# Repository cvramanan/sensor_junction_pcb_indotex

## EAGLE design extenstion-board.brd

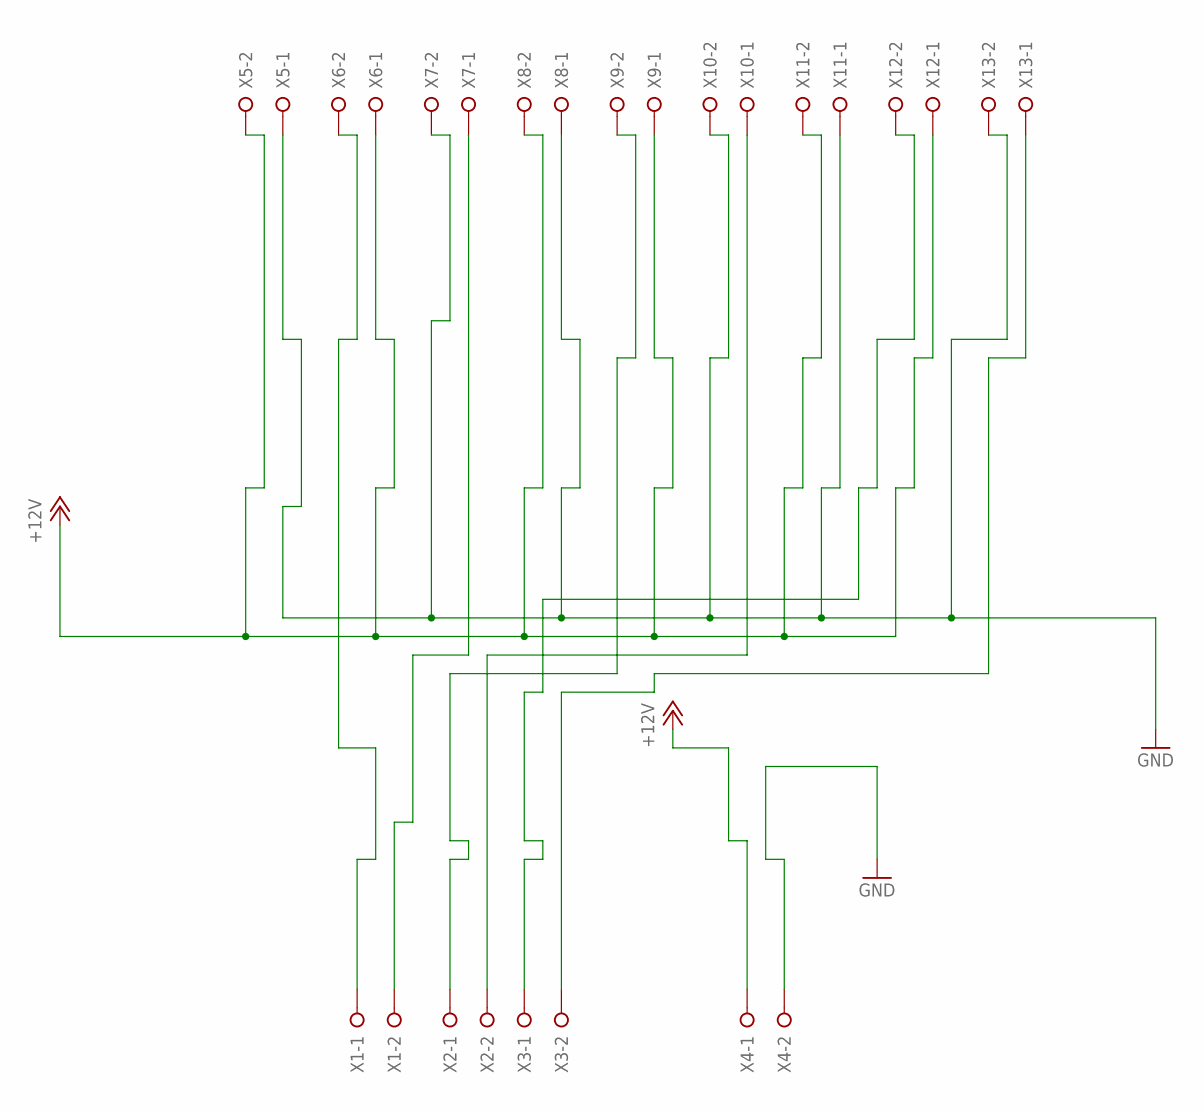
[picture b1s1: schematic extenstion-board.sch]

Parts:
X1, X2, X3, X4, X5, X6, X7, X8, X9, X10, X11, X12, X13: W237-02P; W237-132

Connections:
+12V: X4.1, X5.2, X6.1, X8.2, X9.1, X11.2, X12.1
GND: X4.2, X5.1, X7.2, X8.1, X10.2, X11.1, X13.2
unnamed: X3.1, X12.2
unnamed: X1.1, X6.2
unnamed: X1.2, X7.1
unnamed: X2.1, X9.2
unnamed: X2.2, X10.1
unnamed: X3.2, X13.1

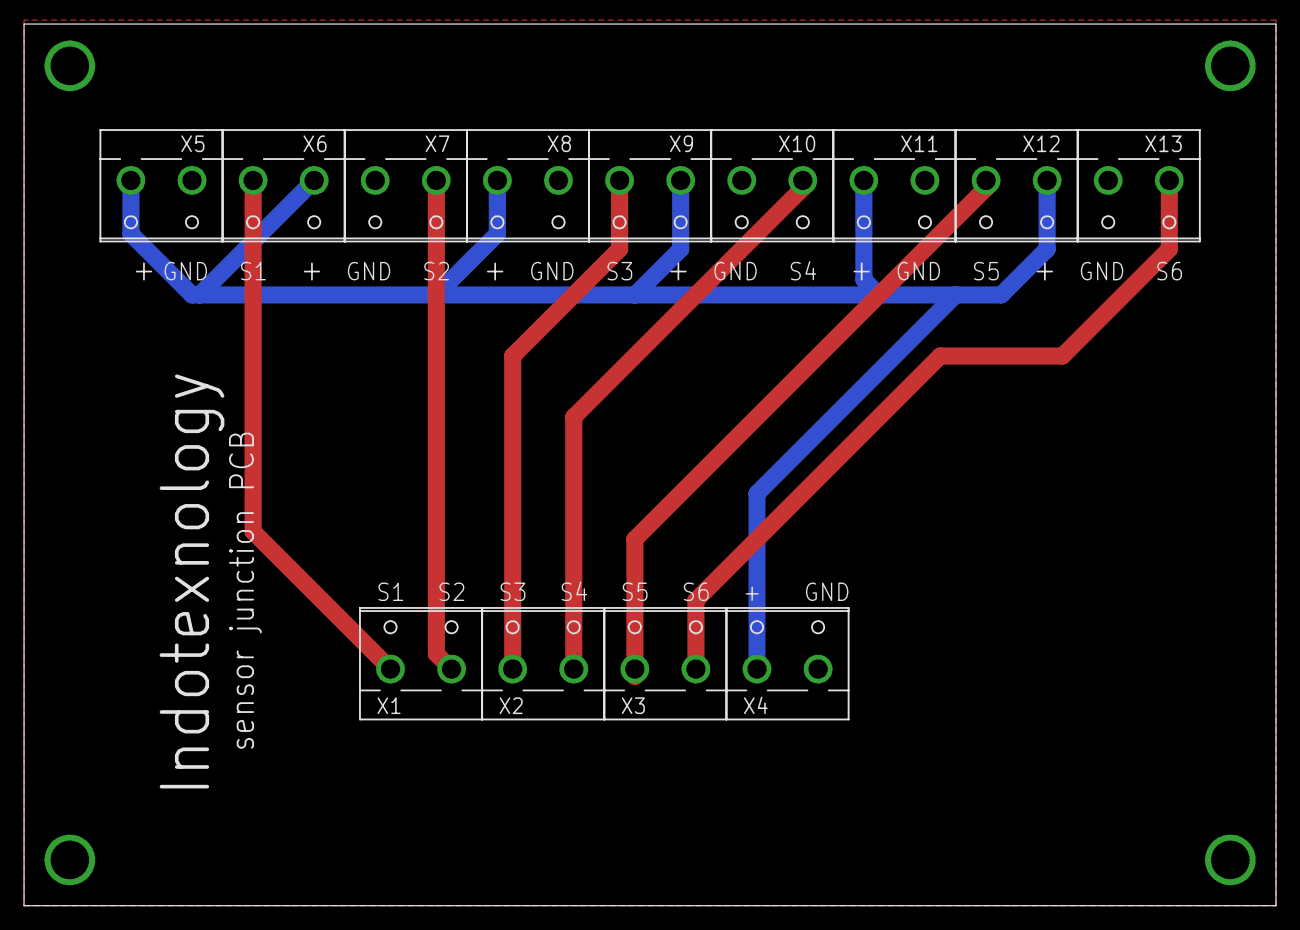
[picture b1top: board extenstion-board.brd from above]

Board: 2 copper layers, 104.1 x 73.3 mm, 13 parts (0 on the bottom side), 8 nets.

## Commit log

2021-08-13 sensor junction pcb with screw holes
2021-10-02 added provision screw plug
2021-10-03 board restructure
2022-02-12 added holes for pillers
